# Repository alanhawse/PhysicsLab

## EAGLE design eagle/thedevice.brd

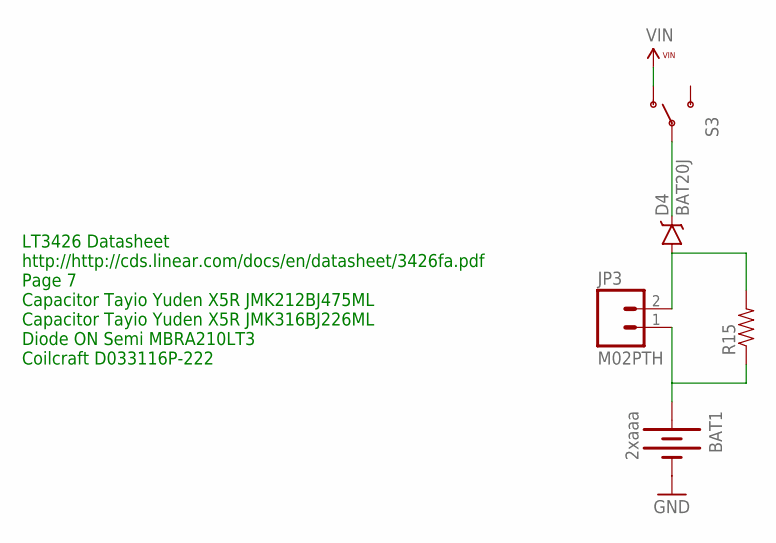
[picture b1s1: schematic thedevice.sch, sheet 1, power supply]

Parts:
BAT1: 2xaaa; BATTERY-2AAA-2468-PTH; PARTNO 2468
D4: BAT20J; SOD-323; PARTNO NSR0320MW2T1G
JP3: M02PTH; 1X02
R15: RESISTOR0603-RES; 0603-RES
S3: SWITCH-SPDTSMD2; SWITCH-SPDT-SMD

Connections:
GND: BAT1.-; also elsewhere on the board
unnamed: BAT1.+, JP3.1, R15.1
unnamed: D4.C, S3.2
unnamed: D4.A, JP3.2, R15.2
VIN: S3.1 (O); also elsewhere on the board

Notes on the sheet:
LT3426 Datasheet http://http://cds.linear.com/docs/en/datasheet/3426fa.pdf Page 7 Capacitor Tayio Yuden X5R JMK212BJ475ML Capacitor Tayio Yuden X5R JMK316BJ226ML Diode ON Semi MBRA210LT3 Coilcraft D033116P-222

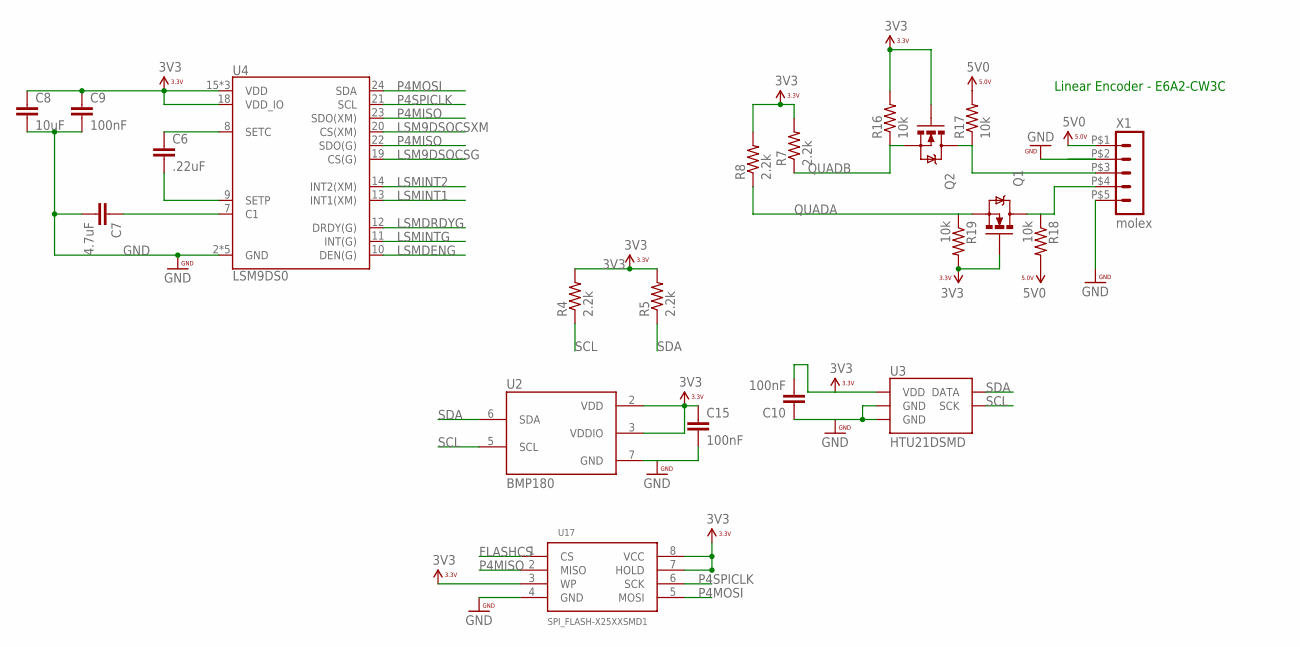
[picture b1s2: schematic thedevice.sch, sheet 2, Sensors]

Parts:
C6: .22uF; 0603-CAP; PARTNO GRM188R61A224KA01D
C7: 4.7uF; 0603-CAP; PARTNO GRM188R60J475KE19D
C8: 10uF; 0603-CAP; PARTNO GRM188R60J106ME47D
C9, C10, C15: 100nF; 0603-CAP; PARTNO GRM188R61E104KA01D
Q1, Q2: MOSFET-NCHANNEL2N7002PW; SOT323
R4, R5, R7, R8: 2.2k; 0603-RES; PARTNO MCR03ERTJ222
R16, R17, R18, R19: 10k; 0603-RES; PARTNO MCR03ERTJ222
U2: BMP180; PARTNO BMP180
U3: HTU21DSMD; HTU21D
U4: LSM9DS0; LGA-24
U17: SPI_FLASH-X25XXSMD1; SO08-EIAJ
X1: molex; 43650-0500; PARTNO 0436500500

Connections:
3V3: C8.1, C9.1, C10.2, C15.1, Q1.1 (G), Q2.1 (G), R4.2, R5.2, R7.2, R8.2, R16.2, R19.2, U2.2 (VDD), U2.3 (VDDIO), U3.VDD, U4.15 (VDD), U4.16 (VDD), U4.17 (VDD), U4.18 (VDD_IO), U17.3 (WP), U17.7 (HOLD), U17.8 (VCC); also elsewhere on the board
5V0: R17.2, R18.2, X1.P$1 (1); also elsewhere on the board
FLASHCS: U17.1 (CS); also elsewhere on the board
GND: C7.2, C8.2, C9.2, C10.1, C15.2, U2.7 (GND), U3.7 (GND), U3.GND, U4.2 (GND), U4.3 (GND), U4.4 (GND), U4.5 (GND), U4.6 (GND), U17.4 (GND), X1.P$2 (2), X1.P$5 (5); also elsewhere on the board
LSM9DSOCSG: U4.19 (CS(G)); also elsewhere on the board
LSM9DSOCSXM: U4.20 (CS(XM)); also elsewhere on the board
LSMDENG: U4.10 (DEN(G)); also elsewhere on the board
LSMDRDYG: U4.12 (DRDY(G)); also elsewhere on the board
LSMINT1: U4.13 (INT1(XM)); also elsewhere on the board
LSMINT2: U4.14 (INT2(XM)); also elsewhere on the board
LSMINTG: U4.11 (INT(G)); also elsewhere on the board
unnamed: C6.2, U4.9 (SETP)
unnamed: C7.1, U4.7 (C1)
unnamed: C6.1, U4.8 (SETC)
unnamed: Q2.3 (D), R17.1, X1.P$3 (3)
unnamed: Q1.3 (D), R18.1, X1.P$4 (4)
P4MISO: U4.22 (SDO(G)), U4.23 (SDO(XM)), U17.2 (MISO); also elsewhere on the board
P4MOSI: U4.24 (SDA), U17.5 (MOSI); also elsewhere on the board
P4SPICLK: U4.21 (SCL), U17.6 (SCK); also elsewhere on the board
QUADA: Q1.2 (S), R8.1, R19.1; also elsewhere on the board
QUADB: Q2.2 (S), R7.1, R16.1; also elsewhere on the board
SCL: R4.1, U2.5 (SCL), U3.SCK; also elsewhere on the board
SDA: R5.1, U2.6 (SDA), U3.DATA; also elsewhere on the board

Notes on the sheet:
Linear Encoder - E6A2-CW3C

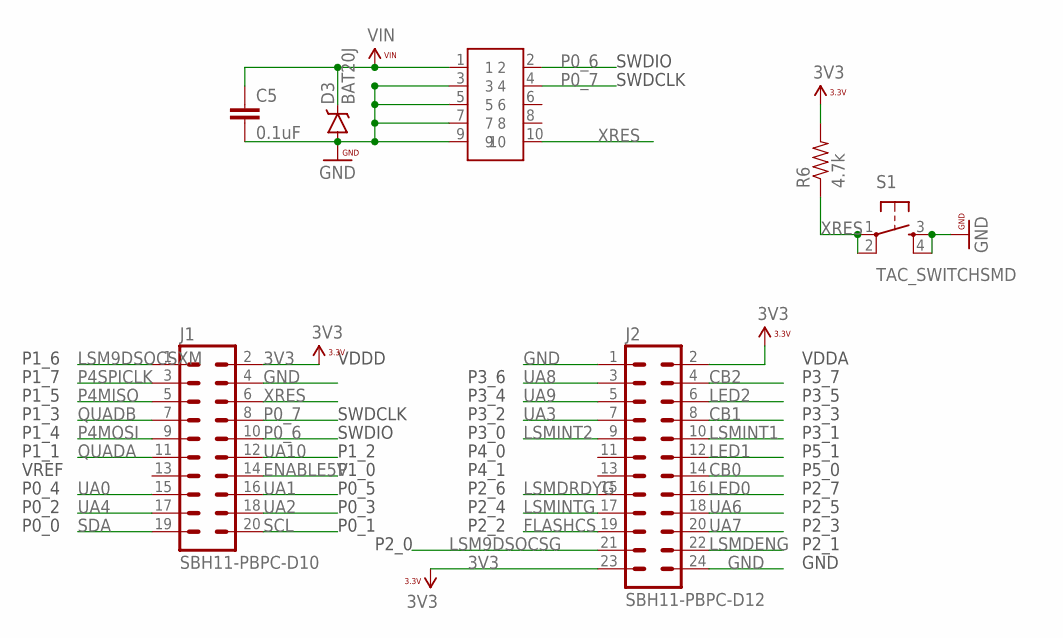
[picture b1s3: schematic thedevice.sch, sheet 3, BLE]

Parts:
C5: 0.1uF; 0603-CAP; PARTNO GRM188R61E104KA01D
D3: BAT20J; SOD-323; PARTNO NSR0320MW2T1G
J1: SBH11-PBPC-D10; PARTNO SBH11-PBPC-D10-ST-BK
J2: SBH11-PBPC-D12; PARTNO SBH11-PBPC-D12-RA-BK
JP: SAMTEC; FTSH-105-01-XXX-DV-K; PARTNO FTSH-105-01-F-DV-K
R6: 4.7k; 0603-RES; PARTNO ERJ-3GEYJ472V
S1: TAC_SWITCHSMD; TACTILE-SWITCH-SMD; PARTNO PTS525SM10SMTR LFS

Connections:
3V3: J1.2, J2.2, J2.23, R6.2; also elsewhere on the board
CB0: J2.14; also elsewhere on the board
CB1: J2.8; also elsewhere on the board
CB2: J2.4; also elsewhere on the board
ENABLE5V: J1.14; also elsewhere on the board
FLASHCS: J2.19; also elsewhere on the board
GND: C5.2, D3.A, J1.4, J2.1, J2.24, JP.3, JP.5, JP.7, JP.9, S1.3, S1.4; also elsewhere on the board
LED0: J2.16; also elsewhere on the board
LED1: J2.12; also elsewhere on the board
LED2: J2.6; also elsewhere on the board
LSM9DSOCSG: J2.21; also elsewhere on the board
LSM9DSOCSXM: J1.1; also elsewhere on the board
LSMDENG: J2.22; also elsewhere on the board
LSMDRDYG: J2.15; also elsewhere on the board
LSMINT1: J2.10; also elsewhere on the board
LSMINT2: J2.9; also elsewhere on the board
LSMINTG: J2.17; also elsewhere on the board
P0_6: J1.10, JP.2
P0_7: J1.8, JP.4
P4MISO: J1.5; also elsewhere on the board
P4MOSI: J1.9; also elsewhere on the board
P4SPICLK: J1.3; also elsewhere on the board
QUADA: J1.11; also elsewhere on the board
QUADB: J1.7; also elsewhere on the board
SCL: J1.20; also elsewhere on the board
SDA: J1.19; also elsewhere on the board
UA0: J1.15; also elsewhere on the board
UA1: J1.16; also elsewhere on the board
UA2: J1.18; also elsewhere on the board
UA3: J2.7; also elsewhere on the board
UA4: J1.17; also elsewhere on the board
UA6: J2.18; also elsewhere on the board
UA7: J2.20; also elsewhere on the board
UA8: J2.3; also elsewhere on the board
UA9: J2.5; also elsewhere on the board
UA10: J1.12; also elsewhere on the board
VIN: C5.1, D3.C, JP.1; also elsewhere on the board
XRES: J1.6, JP.10, R6.1, S1.1, S1.2

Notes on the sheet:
VDDD
VDDA
SWDIO
SWDCLK
P1_2
P1_0
P0_5
P0_3
P0_1
P1_1
VREF
P0_4
P0_2
P0_0
P1_6
P1_7
P1_5
P1_3
P1_4
P4_1
P2_6
P2_4
P2_2
P2_0
P3_6
P3_4
P3_2
P3_0
P4_0
GND
P5_0
P2_7
P2_5
P2_3
P2_1
P3_7
P3_5
P3_3
P3_1
P5_1

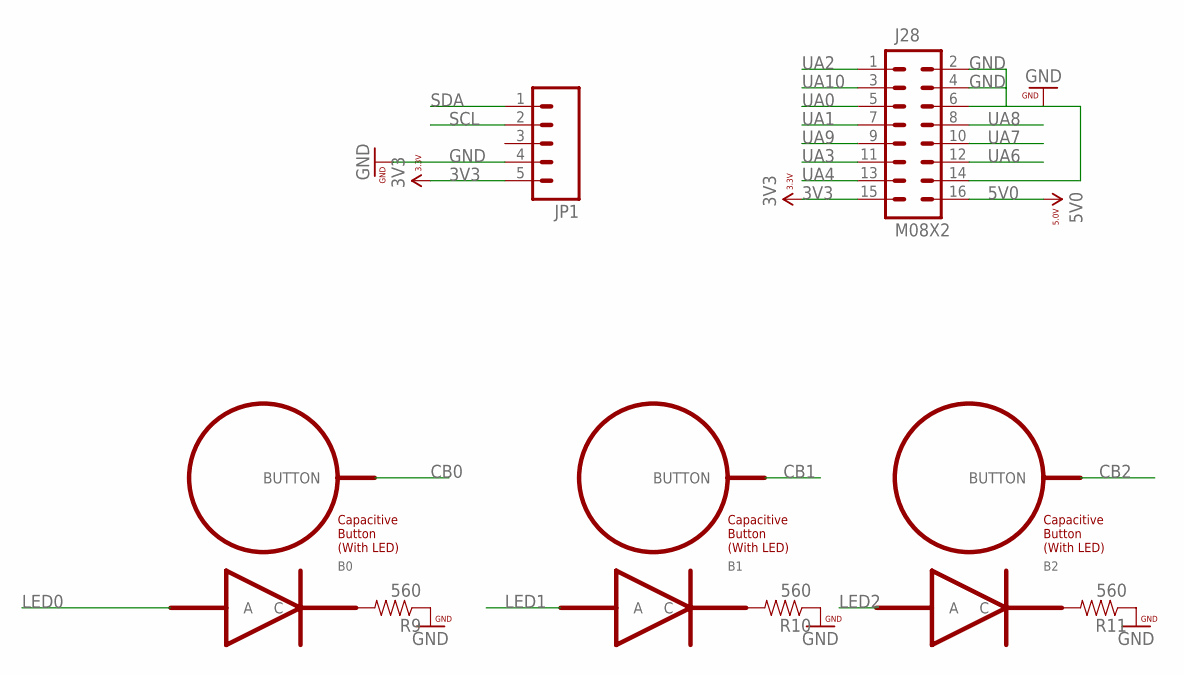
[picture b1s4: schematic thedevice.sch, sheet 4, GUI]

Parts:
B0, B1, B2: BUTTON_PASSIVE_LED; BUTTON_PASSIVE_12MM_LED; PARTNO SML-LX1206IC-TR
J28: M08X2; 2X8
JP1: M05NO_SILK; 1X05_NO_SILK
R9, R10, R11: 560; 0603-RES; PARTNO ERJ-3GEYJ561V

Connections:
3V3: J28.15, JP1.5; also elsewhere on the board
5V0: J28.16; also elsewhere on the board
CB0: B0.BUTTON; also elsewhere on the board
CB1: B1.BUTTON; also elsewhere on the board
CB2: B2.BUTTON; also elsewhere on the board
GND: J28.2, J28.4, J28.6, J28.14, JP1.4, R9.1, R10.1, R11.1; also elsewhere on the board
LED0: B0.A; also elsewhere on the board
LED1: B1.A; also elsewhere on the board
LED2: B2.A; also elsewhere on the board
unnamed: B0.C, R9.2
unnamed: B1.C, R10.2
unnamed: B2.C, R11.2
SCL: JP1.2; also elsewhere on the board
SDA: JP1.1; also elsewhere on the board
UA0: J28.5; also elsewhere on the board
UA1: J28.7; also elsewhere on the board
UA2: J28.1; also elsewhere on the board
UA3: J28.11; also elsewhere on the board
UA4: J28.13; also elsewhere on the board
UA6: J28.12; also elsewhere on the board
UA7: J28.10; also elsewhere on the board
UA8: J28.8; also elsewhere on the board
UA9: J28.9; also elsewhere on the board
UA10: J28.3; also elsewhere on the board

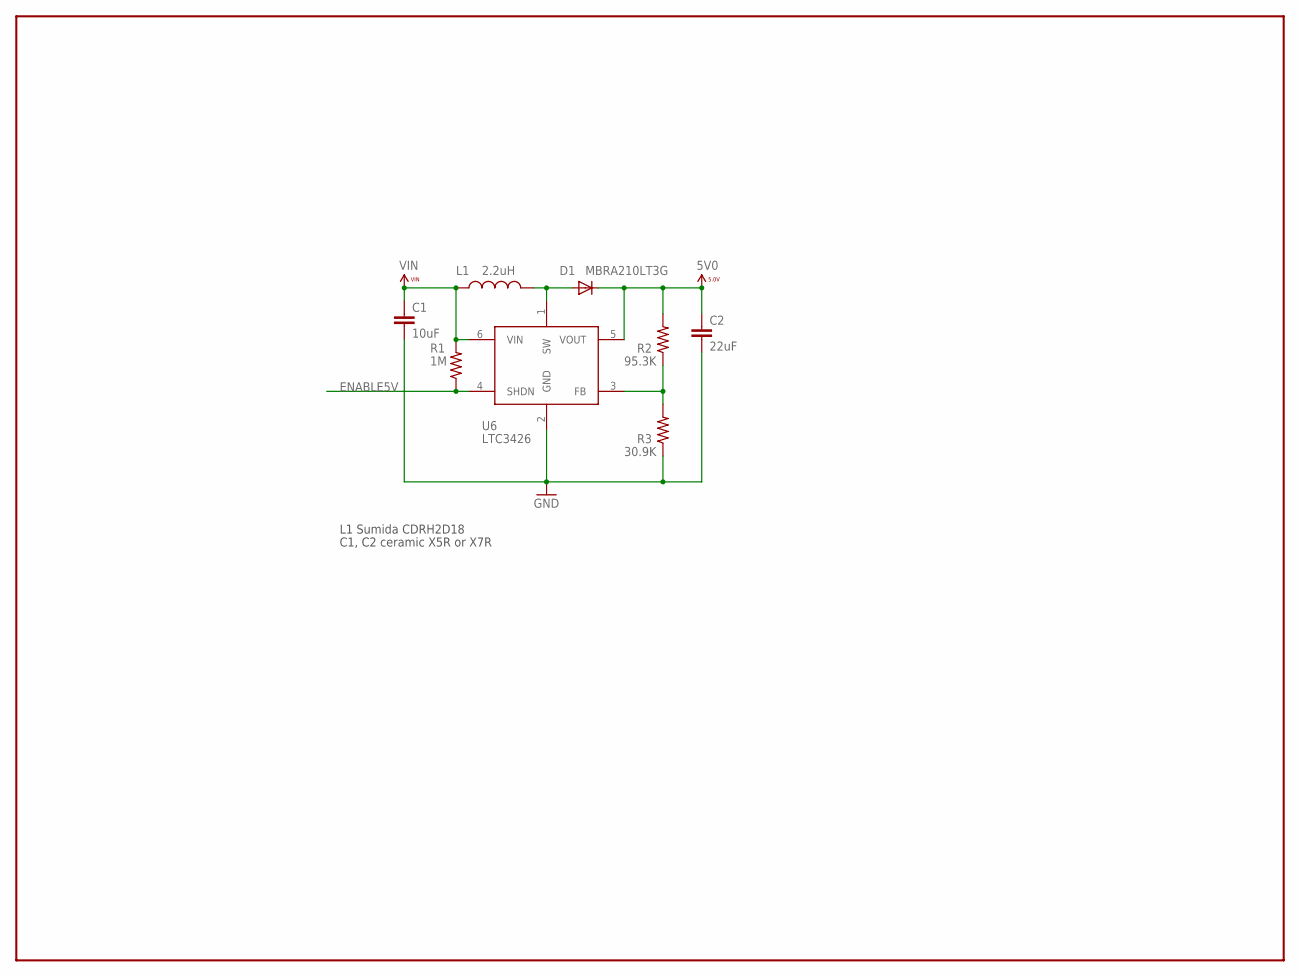
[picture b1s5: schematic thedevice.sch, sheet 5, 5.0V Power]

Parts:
C1: 10uF; 0603-CAP; PARTNO GRM188R60J106ME47D
C2: 22uF; 0603-CAP; PARTNO GRM188R60G226MEA0D
D1: MBRA210LT3G; SMA-DIODE; PARTNO MBRA210LT3G
L1: 2.2uH; 1_3X1_3; PARTNO CDRH2D09NP-2R2MC
R1: 1M; 0603; PARTNO ERJ-3GEYJ105V
R2: 95.3K; 0603; PARTNO ERJ-3EKF9532V
R3: 30.9K; 0603; PARTNO ERJ-3EKF3092V
U6: LTC3426; SOT23-6; PARTNO LTC3426ES6#TRMPBF

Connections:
5V0: C2.1, D1.C, R2.2, U6.5 (VOUT); also elsewhere on the board
ENABLE5V: R1.1, U6.4 (SHDN); also elsewhere on the board
FB5: R2.1, R3.2, U6.3 (FB)
GND: C1.2, C2.2, R3.1, U6.2 (GND); also elsewhere on the board
SW5: D1.A, L1.P$2 (2), U6.1 (SW)
VIN: C1.1, L1.P$1 (1), R1.2, U6.6 (VIN); also elsewhere on the board

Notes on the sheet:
L1 Sumida CDRH2D18
C1, C2 ceramic X5R or X7R

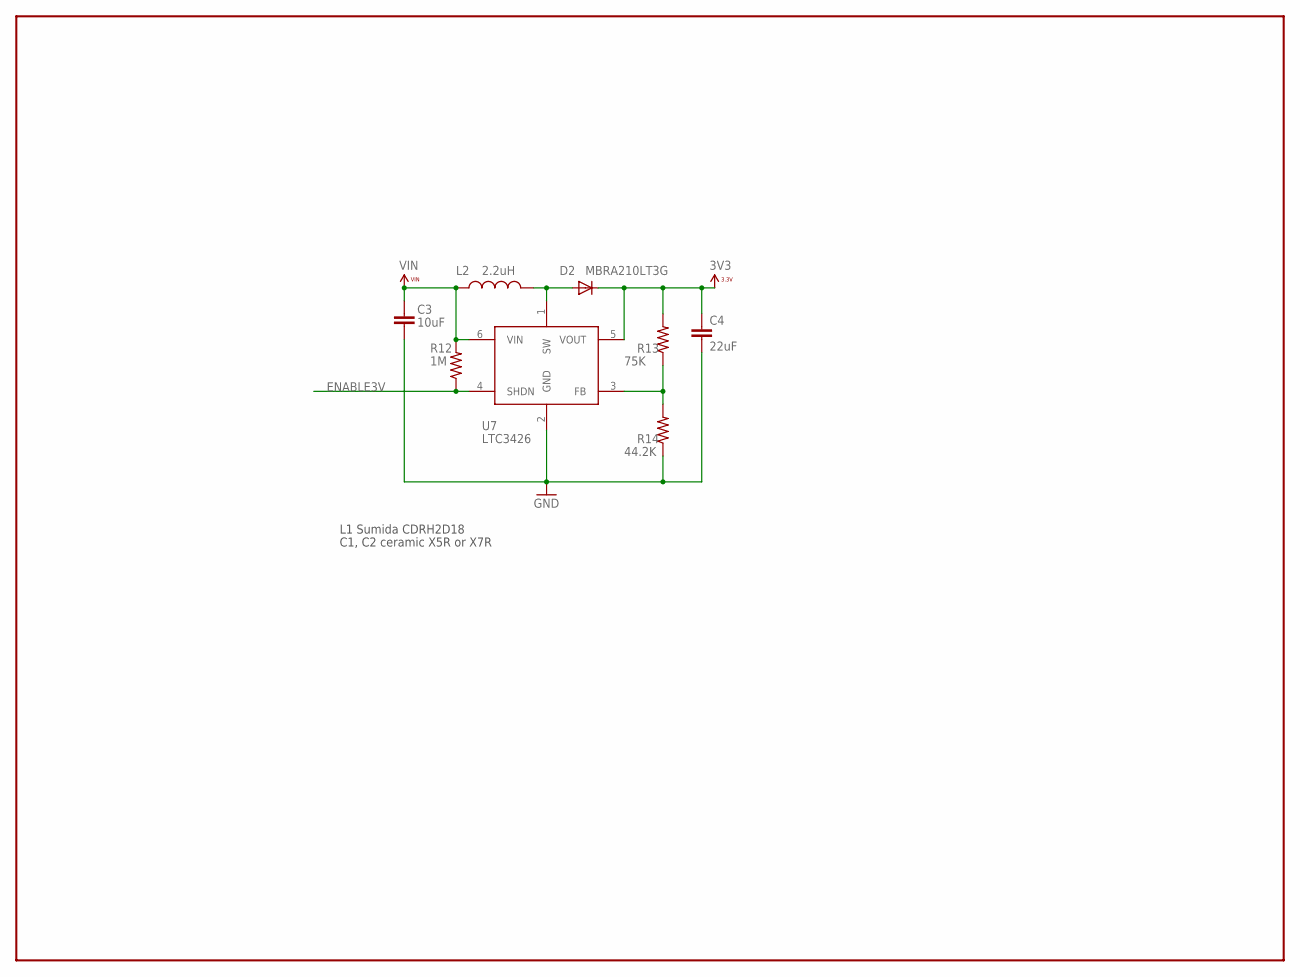
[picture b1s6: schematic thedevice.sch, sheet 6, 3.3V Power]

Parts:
C3: 10uF; 0603; PARTNO GRM188R60J106ME47D
C4: 22uF; 0603-CAP; PARTNO GRM188R60G226MEA0D
D2: MBRA210LT3G; SMA-DIODE; PARTNO MBRA210LT3G
L2: 2.2uH; 1_3X1_3; PARTNO CDRH2D09NP-2R2MC
R12: 1M; 0603; PARTNO ERJ-3GEYJ105V
R13: 75K; 0603; PARTNO ERJ-3EKF7502V
R14: 44.2K; 0603; PARTNO ERJ-3EKF4422V
U7: LTC3426; SOT23-6; PARTNO LTC3426ES6#TRMPBF

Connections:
3V3: C4.1, D2.C, R13.2, U7.5 (VOUT); also elsewhere on the board
ENABLE3V: R12.1, U7.4 (SHDN)
FB3: R13.1, R14.2, U7.3 (FB)
GND: C3.2, C4.2, R14.1, U7.2 (GND); also elsewhere on the board
SW3: D2.A, L2.P$2 (2), U7.1 (SW)
VIN: C3.1, L2.P$1 (1), R12.2, U7.6 (VIN); also elsewhere on the board

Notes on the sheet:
L1 Sumida CDRH2D18
C1, C2 ceramic X5R or X7R

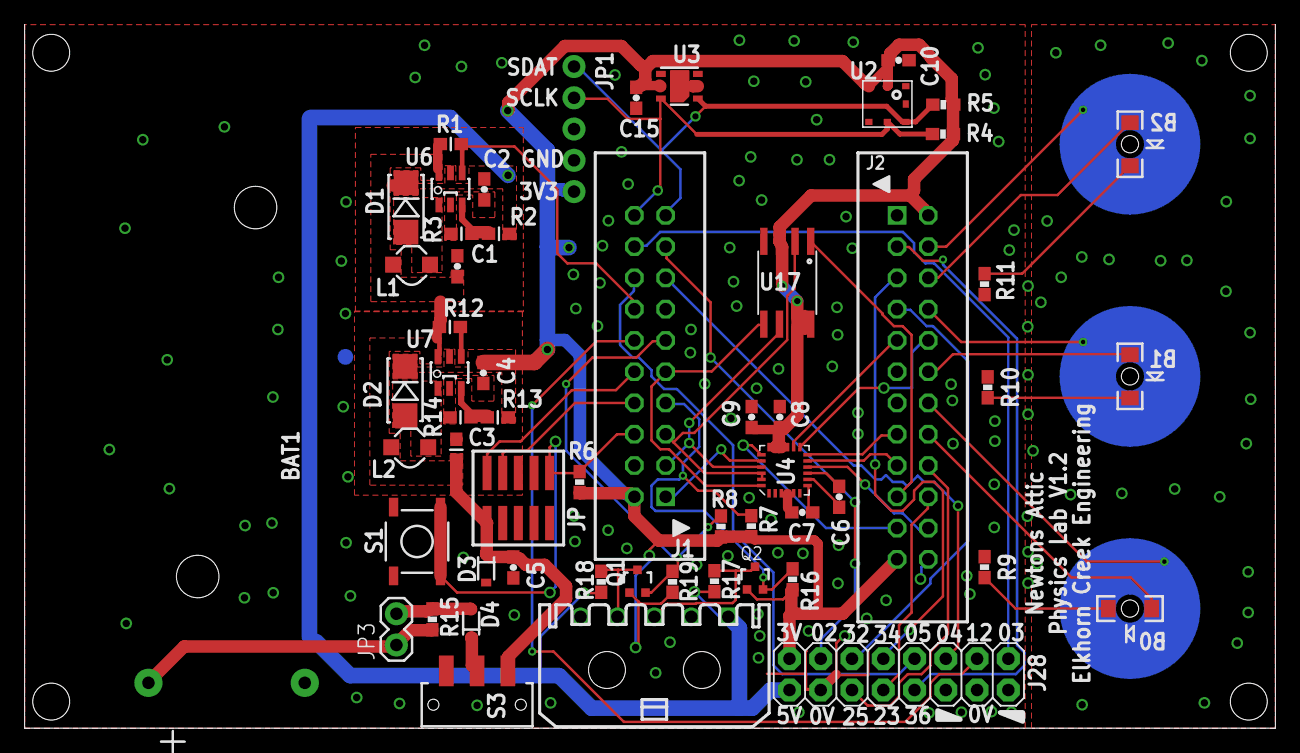
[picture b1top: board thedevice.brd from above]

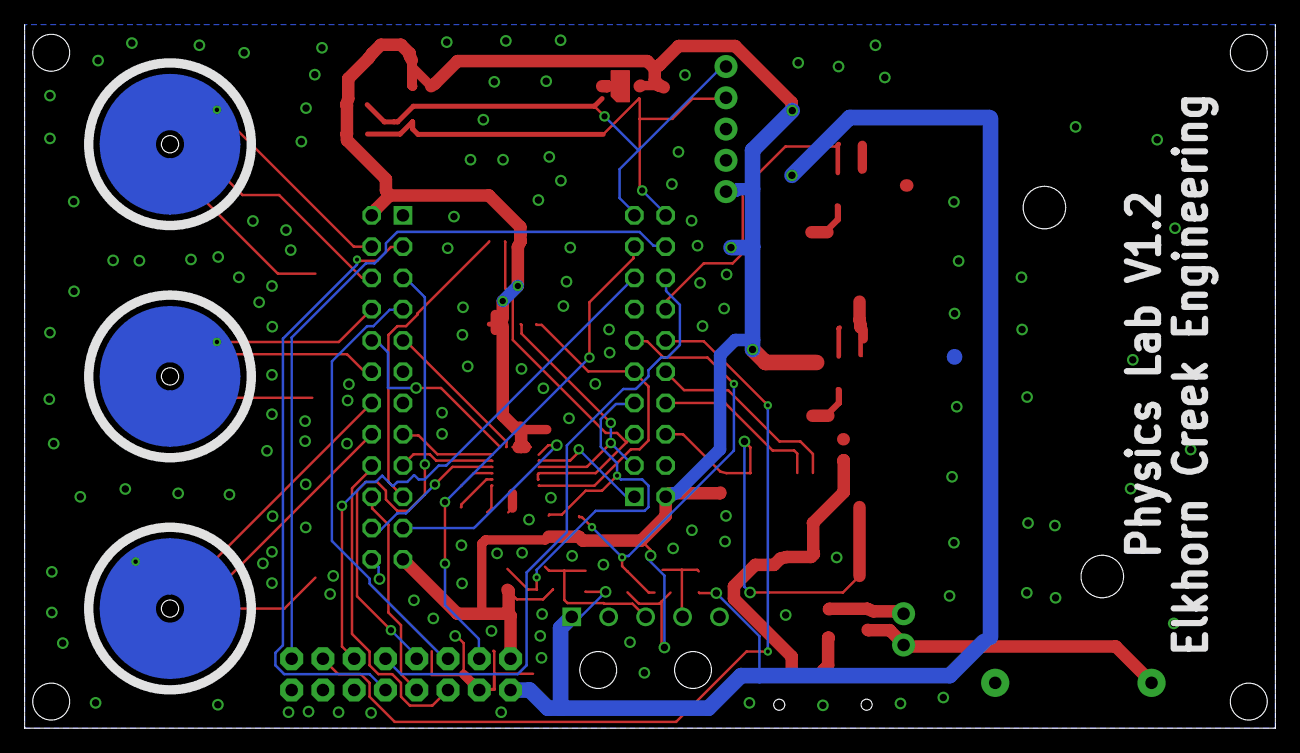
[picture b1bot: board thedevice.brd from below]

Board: 2 copper layers, 101.6 x 57.1 mm, 57 parts (3 on the bottom side), 55 nets.

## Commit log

2015-01-06 first commit. All files represent first tapeout of board
2015-01-11 made all changes for V1.1
2015-01-11 added creator project
2015-01-11 turned on the characteristic values for Temperature, Pressure, Humidity and Altitude
2015-01-26 made a number of updates... right before I completely redo the lsm9ds0 firmware
2015-02-01 Made all V1.2 changes except newtons laws
2015-02-01 Updates for V1.2 ... plus installed the new LSM9DS0 code (which seems to be working)
2015-05-18 first checking
2015-05-27 Fix a bunch of firmware bugs/issues
2015-05-27 added a bunch of features... need to fix a bunch of bugs
2015-06-21 boatloads of updates
2015-06-21 many many updates
2015-06-21 many updates
2015-06-21 changed name of project
2015-06-21 Removed the old administration screen which as replaced with the new tableview screen
2015-06-24 Broke yp physics lab object by dividing out ble advertising and ble connection from the physics lab object
2015-07-12 A boatload of refactoring
2015-07-12 tons of changes
2015-07-12 changes galore
2015-07-13 fixed recording bug
2015-10-31 Fixed advertising
2015-11-21 a shitload of updates
2015-11-21 A bunch of updates
2015-12-09 Added ability to start and stop recording
2015-12-09 Forgot to commit info.plist before releasing.
2015-12-10 Solved issue 55 but adding trackLength and recordingTime to the NSUserDefaults
2015-12-10 Updated color blue on data screen to close issue 50
2015-12-10 Moved environmental titles to standard spacing. Issue 60
2015-12-12 Added packets per second to data screen and graph screen
2015-12-12 Changed timer to whole seconds - Issue 62
2015-12-12 Updated comment
2015-12-12 updated breakpoint
2015-12-12 Added labels to the axis on the graph screen
2015-12-12 RC1 V1.0
2015-12-13 Change max range of velocity to 10m/s and added AppIcon for iPad Pro
2015-12-13 Added 83.5 Icon
2015-12-15 Final commits for version 1.0
2015-12-15 fixed logos
2015-12-17 added pinmap for attempting ble module
2015-12-19 Fixed (well actually worked around) packet scanning rate problem.
2015-12-19 updated build number for packet fix
2015-12-19 Updated documentation on the recording of packets to close issue 46
2015-12-21 First pass example data for the demo.
2015-12-22 intermediate commit demo packets
2015-12-23 first update for demo mode
2015-12-23 2nd round of updates for demo mode
2015-12-23 Data from ARH and WCCIV
2015-12-24 Put in a bunch of playback code. There are several bugs which should be fixed.
2015-12-27 first revision of demo mode
2015-12-27 fixed datafiles
2015-12-28 Fixed zero'ing bug
2015-12-28 put in placeholder for modal popover
2015-12-28 Took out print
2015-12-28 Fixed issue 72... the reset button didnt work on the dashboard view.
2015-12-28 Added position v. time (with bugs on the axes)
2015-12-28 Cleaning up
2015-12-29 Fixed Y range for position, made position default.
2015-12-30 Another attempt to release app
2015-12-30 Updated build #
2015-12-30 updated gitignore to remove *~ and ~*
2015-12-31 change the 0 to 0 to solve issue #79
2016-01-02 fixed a bunch of bugs... way to much for one commit... but oh well
2016-01-02 Updated property observer removal
2016-01-03 Changed delegate methods to be extensions of the base class
2016-01-03 cleaned up NSObject derivations
2016-01-03 Decided that apples ble interface should not be extended to write standard datatypes
2016-01-03 Updated model diagram

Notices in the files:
parts and their libraries:
PatternAgents-TouchWidgets: License : http://creativecommons.org/licenses/by-sa/4.0/ (Creative Commons 4.0)
PatternAgents-TouchWidgets: License : http://creativecommons.org/licenses/by-sa/3.1/ (Creative Commons 3.1)
con-sullins: Copyright (C) 2009, Bob Starr
